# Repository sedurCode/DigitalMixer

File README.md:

View this project on [CADLAB.io](https://cadlab.io/project/1440). 

DigitalMixer

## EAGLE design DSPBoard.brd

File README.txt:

## WEBENCH Design 4
Created at Wed Nov 14 03:32:54 PST 2018
**********************************************************
***************** Schematic Instructions  ****************
**********************************************************

To import your new Schematic file into Eagle:

1. Unzip the downloaded folder files to local directory and Start Eagle.
2. Select "File"->"Open"->"Schematic..." from the menu at the top of
the screen.
3. Browse to your newly exported file and select the ".sch" file extension.
4. You should now see your schamtic available in Eagle.

**********************************************************
*******************  PCB Instructions  *******************
**********************************************************

To import your new BOARD file into Eagle:

1. Unzip the downloaded folder files to local directory and Start Eagle.
2. Select "File"->"Open"->"Board..." from the menu at the top of
the screen.
3. Browse to your newly exported file and select the ".brd" file extension.
4. Planes will need to be repoured to update the polygon fills
	1. Once your board is loaded, type "ratsnest" into the command
	   line and press the Enter key.
	2. The polygons should all be filled now.
5. You should now have an image of your board available in Eagle.

**********************************************************
*******************  LIB Instructions  *******************
**********************************************************

To import your new library into Eagle:

1. Start Eagle.
2. Select "File"->"New"->"Library" from the menu.
3. In the blank library window, select "File" -> "Execute Script"
from the menu.
5. Browse to your newly exported Eagle Script file (".scr" file extension)
6. After opening the file, the script will populate the new library.
Layer 93 should NOT exist.
7. Use "File"->Save As: "AcceleratedDesigns_Lib.lbr" and to the desired
location in Eagle native format.
8. Update schematic with the imported library, Select Library and click on Update; open the library file
	and sync. each part.

For additional information, please visit this site:
http://www.accelerated-designs.com/help/Eagle_import.html

You may also find this video helpful:
http://youtu.be/5jGuWY-Yy3Q

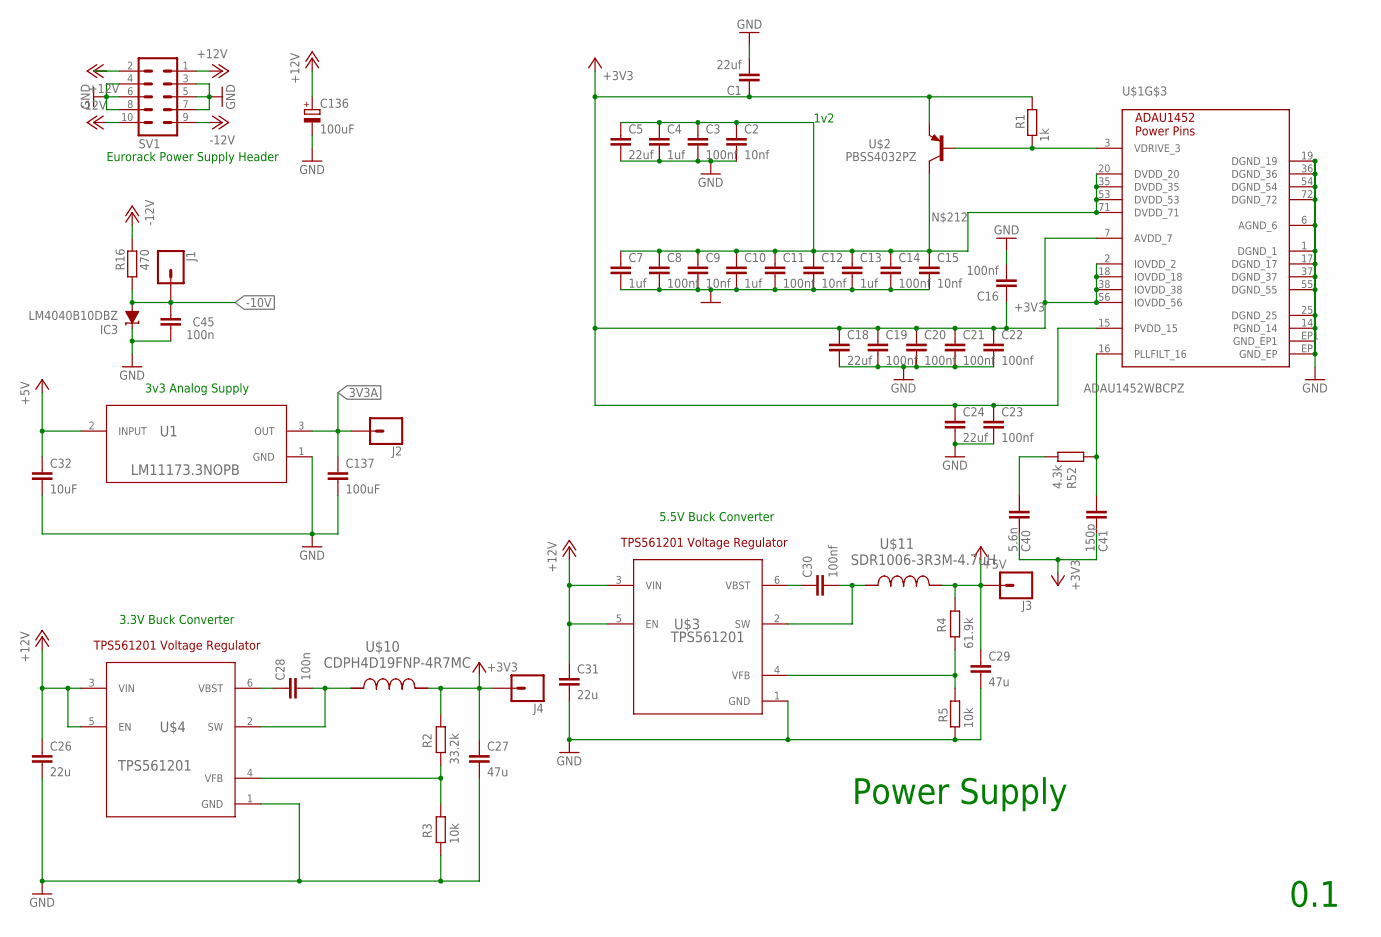
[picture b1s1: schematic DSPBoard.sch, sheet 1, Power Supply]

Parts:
C1, C5, C18, C24: 22uf; C0603
C2, C9, C12, C15: 10nf; C0603
C3, C8, C11, C14, C16, C19, C20, C21, C22, C23, C30: 100nf; C0603
C4, C7, C10, C13: 1uf; C0603
C26, C31: 22u; C0603
C27, C29: 47u; C0603
C28, C45: 100n; C0603
C32: 10uF; C0603
C40: 5.6n; C0603
C41: 150p; C0603
C136: 100uF; PANASONIC_D
C137: 100uF; C0603
IC3: LM4040B10DBZ; DBZ_R-PDSO-G3
J1, J2, J3, J4: CONN_01; 1X01
R1: 1k; R0603
R2: 33.2k; R0603
R3, R5: 10k; R0603
R4: 61.9k; R0603
R16: 470; R0603
R52: 4.3k; R0603
SV1: MA05-2
U1: LM11173.3NOPB; NDP0003B
U$1: ADAU1452WBCPZ; 72-LEADLFCSP_VQ
U$2: PBSS4032PZ; PG-SOT-223
U$3, U$4: TPS561201; DDC0006A
U$10: CDPH4D19FNP-4R7MC; CDPH4D19F
U$11: SDR1006-3R3M-4.7uH; SDR1006

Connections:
3V3A: C137.1, J2.1, U1.3 (OUT); also elsewhere on the board
+3V3: C1.1, C16.1, C18.1, C19.1, C20.1, C21.1, C22.1, C23.1, C24.1, C27.1, C40.2, C41.2, J4.1, R1.2, R2.1, U$1.2 (IOVDD_2), U$1.7 (AVDD_7), U$1.15 (PVDD_15), U$1.18 (IOVDD_18), U$1.38 (IOVDD_38), U$1.56 (IOVDD_56), U$2.3 (EMITTER_3), U$10.2; also elsewhere on the board
+5V: C29.1, C32.1, J3.1, R4.1, U1.2 (INPUT), U$11.2; also elsewhere on the board
+12V: C26.1, C31.1, C136.+, SV1.1, SV1.2, U$3.3 (VIN), U$3.5 (EN), U$4.3 (VIN), U$4.5 (EN); also elsewhere on the board
-10V: C45.2, IC3.2 (A), J1.1, R16.1; also elsewhere on the board
-12V: R16.2, SV1.9, SV1.10; also elsewhere on the board
GND: C1.2, C2.2, C3.2, C4.2, C5.2, C7.2, C8.2, C9.2, C10.2, C11.2, C12.2, C13.2, C14.2, C15.2, C16.2, C18.2, C19.2, C20.2, C21.2, C22.2, C23.2, C24.2, C26.2, C27.2, C29.2, C31.2, C32.2, C45.1, C136.-, C137.2, IC3.1 (C), R3.2, R5.2, SV1.3, SV1.4, SV1.5, SV1.6, SV1.7, SV1.8, U1.1 (GND), U$1.1 (DGND_1), U$1.6 (AGND_6), U$1.14 (PGND_14), U$1.17 (DGND_17), U$1.19 (DGND_19), U$1.25 (DGND_25), U$1.36 (DGND_36), U$1.37 (DGND_37), U$1.54 (DGND_54), U$1.55 (DGND_55), U$1.72 (DGND_72), U$1.EP (GND_EP), U$1.EP1 (GND_EP1), U$3.1 (GND), U$4.1 (GND); also elsewhere on the board
unnamed: R1.1, U$1.3 (VDRIVE_3), U$2.1 (BASE_1)
unnamed: C30.1, U$3.6 (VBST)
unnamed: C28.1, U$4.6 (VBST)
unnamed: C28.2, U$4.2 (SW), U$10.1
unnamed: C30.2, U$3.2 (SW), U$11.1
unnamed: R2.2, R3.1, U$4.4 (VFB)
unnamed: R4.2, R5.1, U$3.4 (VFB)
unnamed: C41.1, R52.2, U$1.16 (PLLFILT_16)
unnamed: C40.1, R52.1
unnamed: C2.1, C3.1, C4.1, C5.1, C7.1, C8.1, C9.1, C10.1, C11.1, C12.1, C13.1, C14.1, C15.1, U$1.20 (DVDD_20), U$1.35 (DVDD_35), U$1.53 (DVDD_53), U$1.71 (DVDD_71), U$2.2 (COLLECTOR_2,4), U$2.4 (COLLECTOR_2,4)

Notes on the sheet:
Power Supply
Eurorack Power Supply Header
5.5V Buck Converter
3.3V Buck Converter
3v3 Analog Supply
0.1
1v2

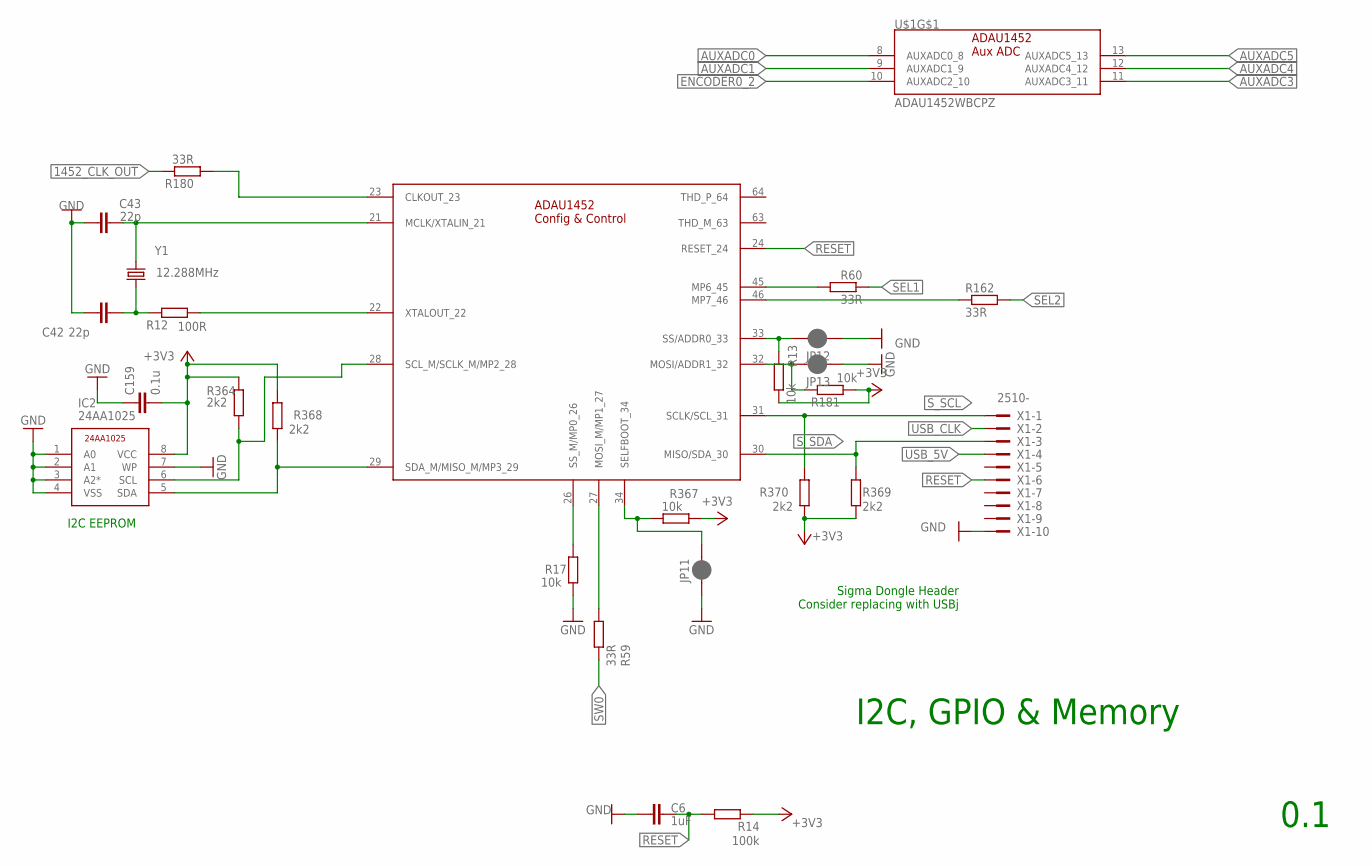
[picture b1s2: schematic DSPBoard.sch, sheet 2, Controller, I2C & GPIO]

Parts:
C6: 1uF; C0603
C42, C43: 22p; C0603
C159: 0.1u; C0603
IC2: 24AA1025; SOIC8
JP11, JP12, JP13: JUMPER-SMT_2_NC_PASTE_SILK; SMT-JUMPER_2_NC_PASTE_SILK
R12: 100R; R0603
R13, R17, R181, R367: 10k; R0603
R14: 100k; R0603
R59, R60, R162, R180: 33R; R0603
R364, R368, R369, R370: 2k2; R0603
U$1: ADAU1452WBCPZ; 72-LEADLFCSP_VQ
X1: 2510-; PAK100/2500-10
Y1: 12.288MHz; CRYSTAL-SMD-5X3.2-4PAD

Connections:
1452_CLK_OUT: R180.2; also elsewhere on the board
+3V3: C159.2, IC2.8 (VCC), R13.1, R14.2, R181.1, R364.2, R367.2, R368.1, R369.1, R370.1; also elsewhere on the board
AUXADC0: U$1.8 (AUXADC0_8); also elsewhere on the board
AUXADC1: U$1.9 (AUXADC1_9)
AUXADC3: U$1.11 (AUXADC3_11)
AUXADC4: U$1.12 (AUXADC4_12)
AUXADC5: U$1.13 (AUXADC5_13)
ENCODER0_2: U$1.10 (AUXADC2_10)
GND: C6.2, C42.1, C43.1, C159.1, IC2.1 (A0), IC2.2 (A1), IC2.3 (A2*), IC2.4 (VSS), IC2.7 (WP), JP11.1, JP12.1, JP13.1, R17.2, X1.10; also elsewhere on the board
MP0: R17.1, U$1.26 (SS_M/MP0_26)
MP1: R59.1, U$1.27 (MOSI_M/MP1_27)
MP2: IC2.6 (SCL), R364.1, U$1.28 (SCL_M/SCLK_M/MP2_28)
MP3: IC2.5 (SDA), R368.2, U$1.29 (SDA_M/MISO_M/MP3_29)
MP6: R60.2, U$1.45 (MP6_45)
MP7: R162.1, U$1.46 (MP7_46)
unnamed: R12.2, U$1.22 (XTALOUT_22)
unnamed: C43.2, U$1.21 (MCLK/XTALIN_21), Y1.3 (2)
unnamed: C42.2, R12.1, Y1.1
unnamed: R180.1, U$1.23 (CLKOUT_23)
unnamed: JP12.2, R13.2, U$1.33 (SS/ADDR0_33)
unnamed: JP13.2, R181.2, U$1.32 (MOSI/ADDR1_32)
unnamed: JP11.2, R367.1, U$1.34 (SELFBOOT_34)
RESET: C6.1, R14.1, U$1.24 (RESET_24), X1.6; also elsewhere on the board
SEL1: R60.1; also elsewhere on the board
SEL2: R162.2; also elsewhere on the board
SW0: R59.2; also elsewhere on the board
S_SCL: R370.2, U$1.31 (SCLK/SCL_31), X1.1; also elsewhere on the board
S_SDA: R369.2, U$1.30 (MISO/SDA_30), X1.3; also elsewhere on the board
USB_5V: X1.4
USB_CLK: X1.2

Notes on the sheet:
I2C EEPROM
Sigma Dongle Header Consider replacing with USBj
0.1
I2C, GPIO & Memory

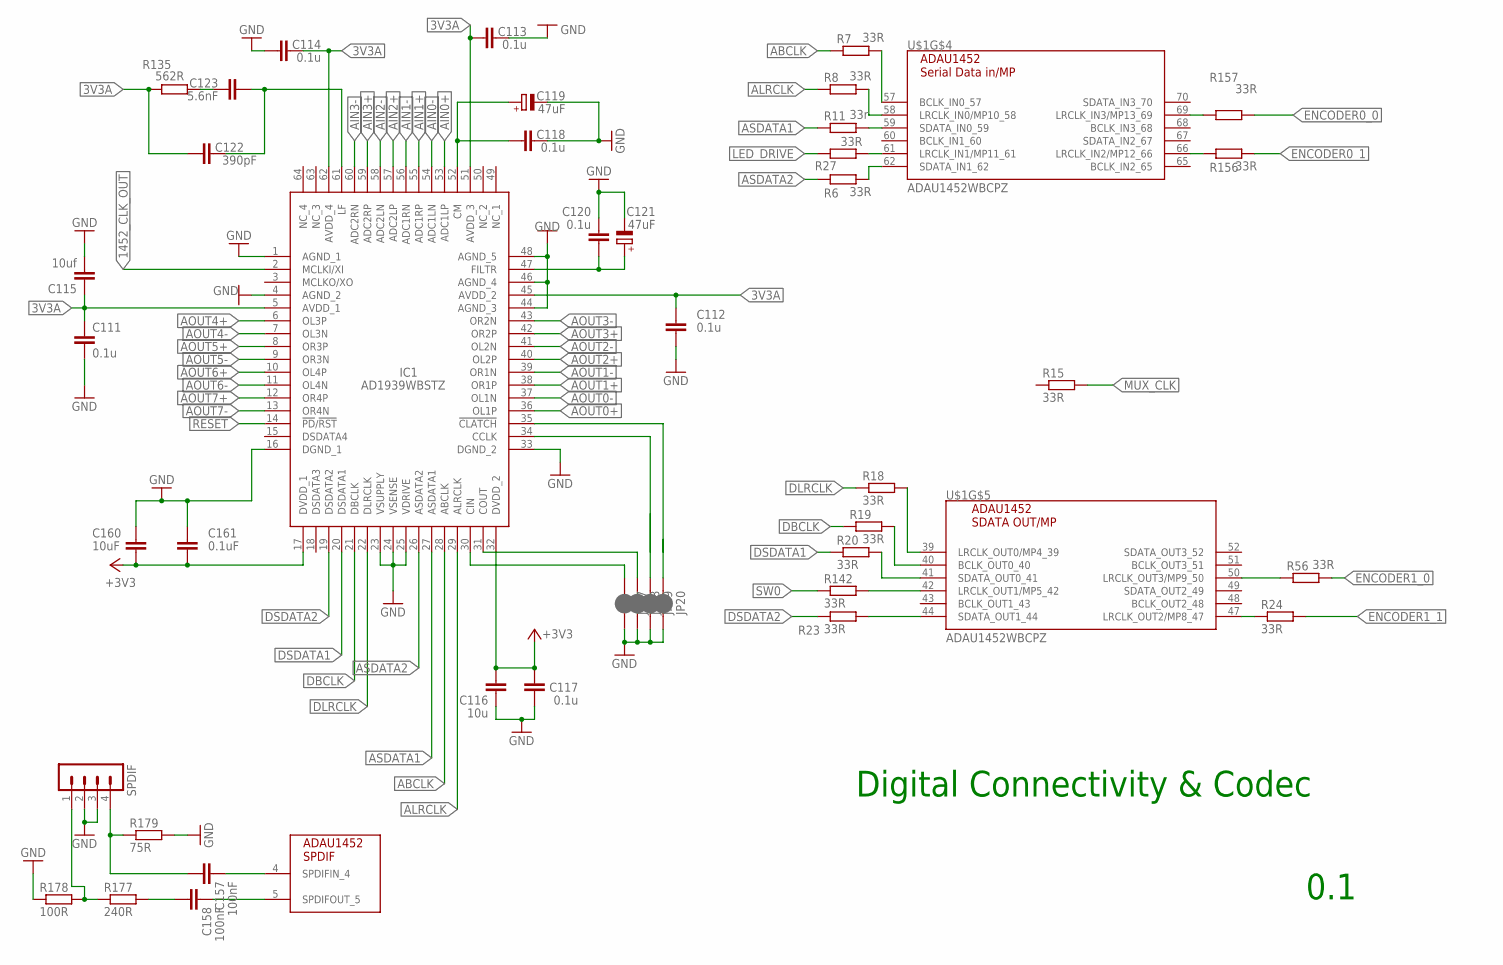
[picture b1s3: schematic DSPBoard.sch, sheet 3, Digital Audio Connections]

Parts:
C111, C112, C113, C114, C117, C118, C120: 0.1u; C0603
C115: 10uf; C0603
C116: 10u; C0603
C119, C121: 47uF; PANASONIC_D
C122: 390pF; C0603
C123: 5.6nF; C0603
C157, C158: 100nF; C0603
C160: 10uF; C0603
C161: 0.1uF; C0603
IC1: AD1939WBSTZ; QFP50P1200X1200X160-64N
JP17, JP18, JP19, JP20: JUMPER-SMT_2_NC_PASTE_SILK; SMT-JUMPER_2_NC_PASTE_SILK
R6, R7, R8, R15, R18, R19, R20, R23, R24, R27, R56, R142, R156, R157: 33R; R0603
R11: 33r; R0603
R135: 562R; R0603
R177: 240R; R0603
R178: 100R; R0603
R179: 75R; R0603
SPDIF: MA04-1
U$1: ADAU1452WBCPZ; 72-LEADLFCSP_VQ

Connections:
3V3A: C111.1, C112.1, C113.1, C114.2, C115.1, C122.1, IC1.5 (AVDD_1), IC1.45 (AVDD_2), IC1.51 (AVDD_3), IC1.62 (AVDD_4), R135.1; also elsewhere on the board
1452_CLK_OUT: IC1.2 (MCLKI/XI); also elsewhere on the board
+3V3: C116.2, C117.2, C160.2, C161.2, IC1.17 (DVDD_1), IC1.32 (DVDD_2); also elsewhere on the board
ABCLK: IC1.28 (ABCLK), R7.1
AIN0+: IC1.53 (ADC1LP); also elsewhere on the board
AIN0-: IC1.54 (ADC1LN); also elsewhere on the board
AIN1+: IC1.55 (ADC1RP); also elsewhere on the board
AIN1-: IC1.56 (ADC1RN); also elsewhere on the board
AIN2+: IC1.57 (ADC2LP); also elsewhere on the board
AIN2-: IC1.58 (ADC2LN); also elsewhere on the board
AIN3+: IC1.59 (ADC2RP); also elsewhere on the board
AIN3-: IC1.60 (ADC2RN); also elsewhere on the board
ALRCLK: IC1.29 (ALRCLK), R8.1
AOUT0+: IC1.36 (OL1P); also elsewhere on the board
AOUT0-: IC1.37 (OL1N); also elsewhere on the board
AOUT1+: IC1.38 (OR1P); also elsewhere on the board
AOUT1-: IC1.39 (OR1N); also elsewhere on the board
AOUT2+: IC1.40 (OL2P); also elsewhere on the board
AOUT2-: IC1.41 (OL2N); also elsewhere on the board
AOUT3+: IC1.42 (OR2P); also elsewhere on the board
AOUT3-: IC1.43 (OR2N); also elsewhere on the board
AOUT4+: IC1.6 (OL3P); also elsewhere on the board
AOUT4-: IC1.7 (OL3N); also elsewhere on the board
AOUT5+: IC1.8 (OR3P); also elsewhere on the board
AOUT5-: IC1.9 (OR3N); also elsewhere on the board
AOUT6+: IC1.10 (OL4P); also elsewhere on the board
AOUT6-: IC1.11 (OL4N); also elsewhere on the board
AOUT7+: IC1.12 (OR4P); also elsewhere on the board
AOUT7-: IC1.13 (OR4N); also elsewhere on the board
ASDATA1: IC1.27 (ASDATA1), R11.1
ASDATA2: IC1.26 (ASDATA2), R6.1
DBCLK: IC1.21 (DBCLK), R19.1
DLRCLK: IC1.22 (DLRCLK), R18.1
DSDATA1: IC1.20 (DSDATA1), R20.1
DSDATA2: IC1.19 (DSDATA2), R23.1
DSP_47: R24.1, U$1.47 (LRCLK_OUT2/MP8_47)
DSP_50: R56.1, U$1.50 (LRCLK_OUT3/MP9_50)
ENCODER0_0: R157.2; also elsewhere on the board
ENCODER0_1: R156.2; also elsewhere on the board
ENCODER1_0: R56.2; also elsewhere on the board
ENCODER1_1: R24.2; also elsewhere on the board
FILTR: C120.1, C121.+, IC1.47 (FILTR)
GND: C111.2, C112.2, C113.2, C114.1, C115.2, C116.1, C117.1, C118.2, C119.-, C120.2, C121.-, C160.1, C161.1, IC1.1 (AGND_1), IC1.4 (AGND_2), IC1.16 (DGND_1), IC1.23 (VSUPPLY), IC1.24 (VSENSE), IC1.25 (VDRIVE), IC1.33 (DGND_2), IC1.44 (AGND_3), IC1.46 (AGND_4), IC1.48 (AGND_5), JP17.2, JP18.2, JP19.2, JP20.2, R178.1, R179.2, SPDIF.2, SPDIF.3; also elsewhere on the board
LED_DRIVE: R27.2; also elsewhere on the board
MP4: R18.2, U$1.39 (LRCLK_OUT0/MP4_39)
MP5: R142.2, U$1.42 (LRCLK_OUT1/MP5_42)
MP10: R8.2, U$1.58 (LRCLK_IN0/MP10_58)
MP11: R27.1, U$1.61 (LRCLK_IN1/MP11_61)
MUX_CLK: R15.2; also elsewhere on the board
unnamed: IC1.30 (CIN), JP17.1
unnamed: R156.1, U$1.66 (LRCLK_IN2/MP12_66)
unnamed: R157.1, U$1.69 (LRCLK_IN3/MP13_69)
unnamed: C157.1, U$1.4 (SPDIFIN_4)
unnamed: C158.1, U$1.5 (SPDIFOUT_5)
unnamed: R6.2, U$1.62 (SDATA_IN1_62)
unnamed: C157.2, R179.1, SPDIF.4
unnamed: C118.1, C119.+, IC1.52 (CM)
unnamed: R7.2, U$1.57 (BCLK_IN0_57)
unnamed: C123.1, R135.2
unnamed: C122.2, C123.2, IC1.61 (LF)
unnamed: R11.2, U$1.59 (SDATA_IN0_59)
unnamed: R23.2, U$1.44 (SDATA_OUT1_44)
unnamed: R20.2, U$1.41 (SDATA_OUT0_41)
unnamed: R19.2, U$1.40 (BCLK_OUT0_40)
unnamed: C158.2, R177.2
unnamed: R177.1, R178.2, SPDIF.1
unnamed: IC1.31 (COUT), JP18.1
RESET: IC1.14 (!PD!/!RST); also elsewhere on the board
SW0: R142.1; also elsewhere on the board

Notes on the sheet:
0.1
Digital Connectivity & Codec

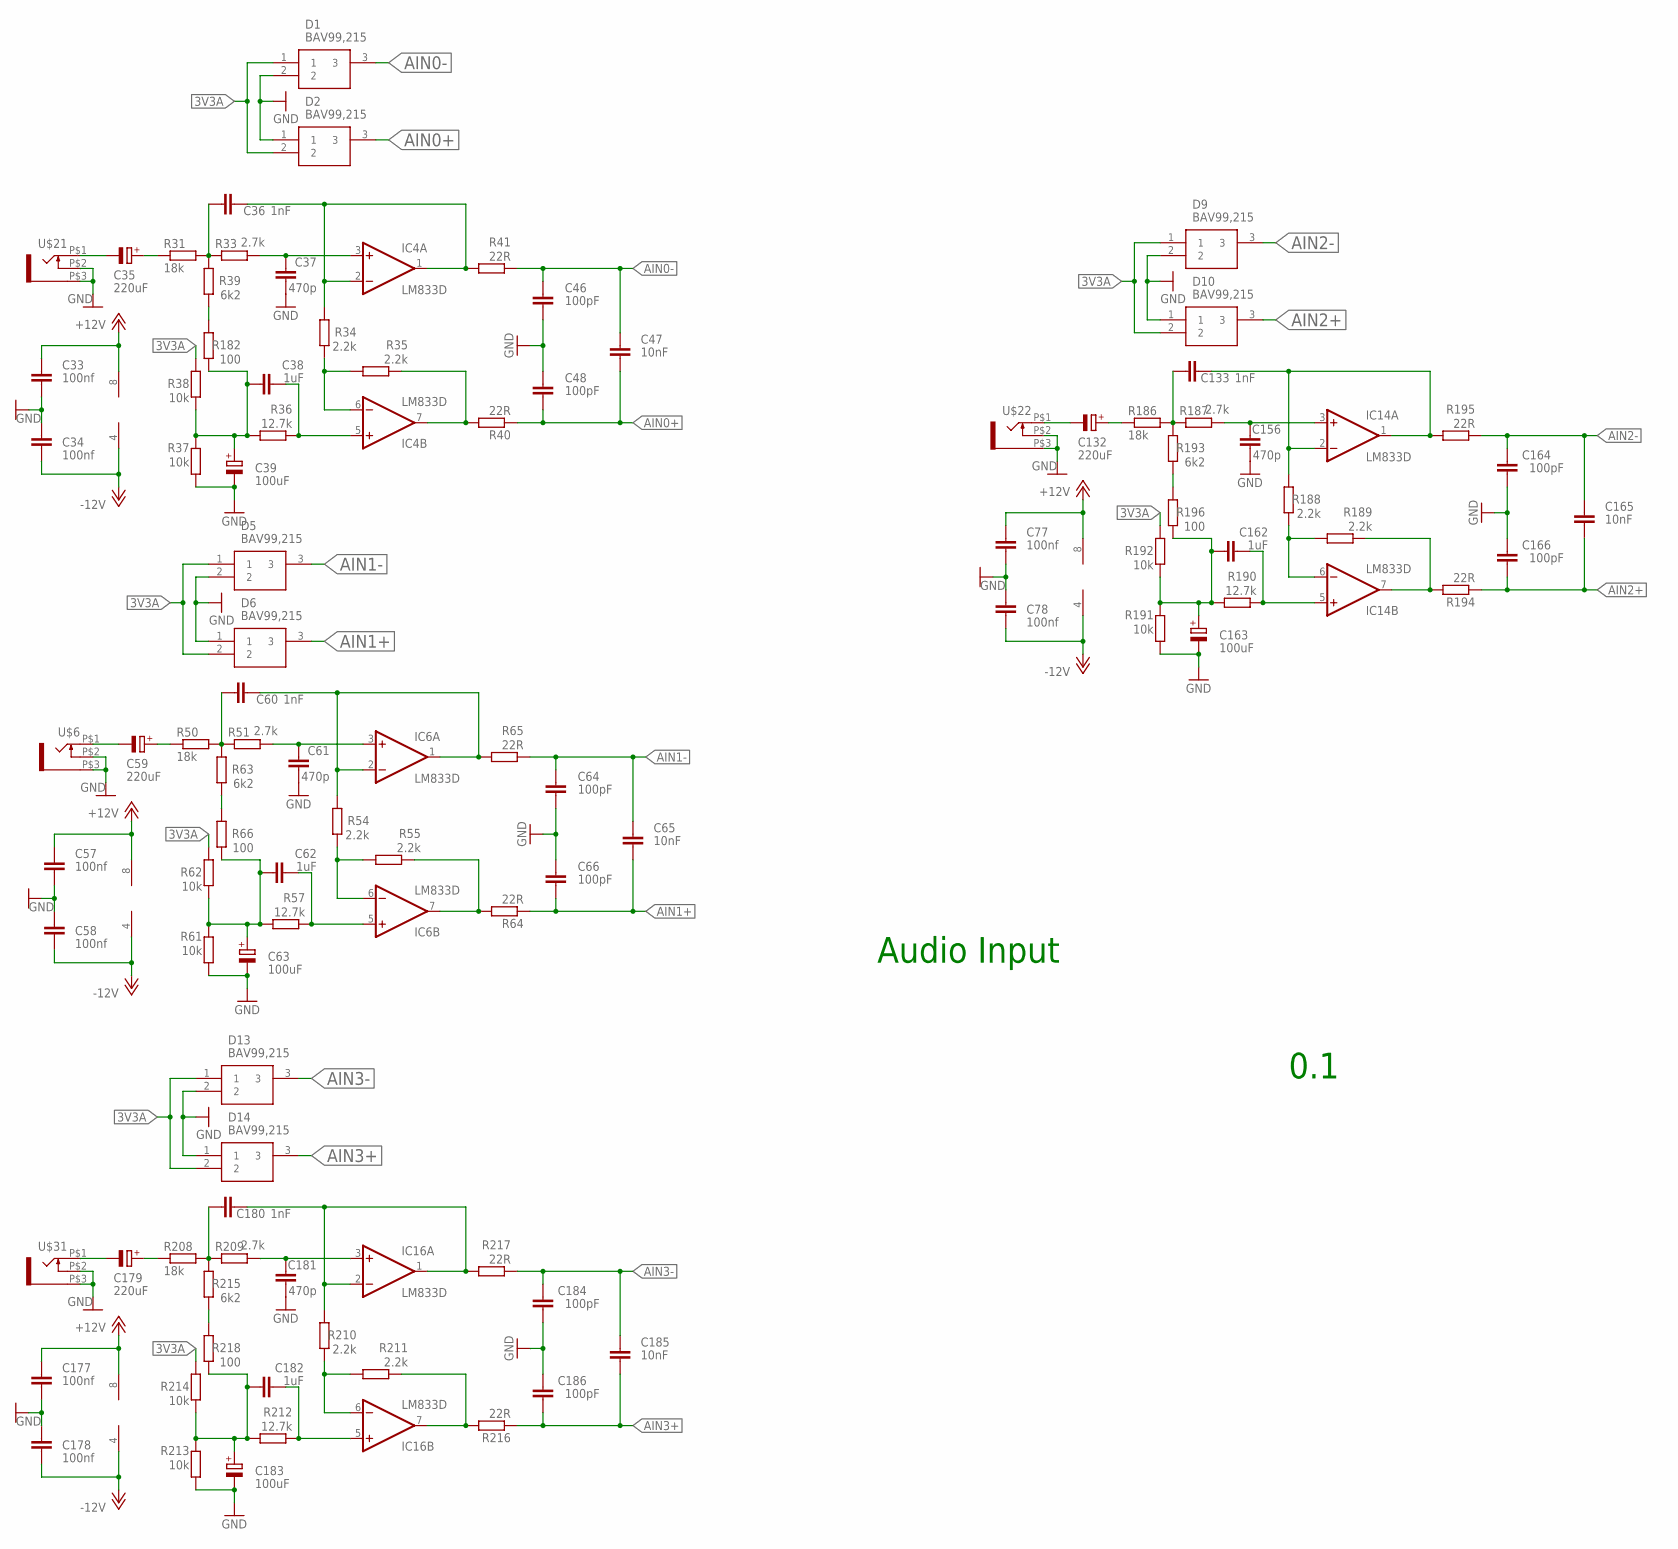
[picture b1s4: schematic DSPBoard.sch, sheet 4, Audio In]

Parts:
C33, C34, C57, C58, C77, C78, C177, C178: 100nf; C0603
C35, C59, C132, C179: 220uF; PANASONIC_D
C36, C60, C133, C180: 1nF; C0603
C37, C61, C156, C181: 470p; C0603
C38, C62, C162, C182: 1uF; C0603
C39, C63, C163, C183: 100uF; PANASONIC_D
C46, C48, C64, C66, C164, C166, C184, C186: 100pF; C0603
C47, C65, C165, C185: 10nF; C0603
D1, D2, D5, D6, D9, D10, D13, D14: BAV99,215; SOT95P230X110-3N
IC4, IC6, IC14, IC16: LM833D; SO08
R31, R50, R186, R208: 18k; R0603
R33, R51, R187, R209: 2.7k; R0603
R34, R35, R54, R55, R188, R189, R210, R211: 2.2k; R0603
R36, R57, R190, R212: 12.7k; R0603
R37, R38, R61, R62, R191, R192, R213, R214: 10k; R0603
R39, R63, R193, R215: 6k2; R0603
R40, R41, R64, R65, R194, R195, R216, R217: 22R; R0603
R66, R182, R196, R218: 100; R0603
U$6, U$21, U$22, U$31: WQP-PJ301M-12_JACK

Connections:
3V3A: D1.1, D2.2, D5.1, D6.2, D9.1, D10.2, D13.1, D14.2, R38.2, R62.2, R192.2, R214.2; also elsewhere on the board
+12V: C33.1, C57.1, C77.1, C177.1, IC4.8 (V+), IC6.8 (V+), IC14.8 (V+), IC16.8 (V+); also elsewhere on the board
-12V: C34.2, C58.2, C78.2, C178.2, IC4.4 (V-), IC6.4 (V-), IC14.4 (V-), IC16.4 (V-); also elsewhere on the board
AIN0+: C47.2, C48.1, D2.3, R40.1; also elsewhere on the board
AIN0-: C46.2, C47.1, D1.3, R41.1; also elsewhere on the board
AIN1+: C65.2, C66.1, D6.3, R64.1; also elsewhere on the board
AIN1-: C64.2, C65.1, D5.3, R65.1; also elsewhere on the board
AIN2+: C165.2, C166.1, D10.3, R194.1; also elsewhere on the board
AIN2-: C164.2, C165.1, D9.3, R195.1; also elsewhere on the board
AIN3+: C185.2, C186.1, D14.3, R216.1; also elsewhere on the board
AIN3-: C184.2, C185.1, D13.3, R217.1; also elsewhere on the board
GND: C33.2, C34.1, C37.1, C39.-, C46.1, C48.2, C57.2, C58.1, C61.1, C63.-, C64.1, C66.2, C77.2, C78.1, C156.1, C163.-, C164.1, C166.2, C177.2, C178.1, C181.1, C183.-, C184.1, C186.2, D1.2, D2.1, D5.2, D6.1, D9.2, D10.1, D13.2, D14.1, R37.1, R61.1, R191.1, R213.1, U$6.P$2 (3), U$6.P$3 (1), U$21.P$2 (3), U$21.P$3 (1), U$22.P$2 (3), U$22.P$3 (1), U$31.P$2 (3), U$31.P$3 (1); also elsewhere on the board
unnamed: C35.-, U$21.P$1 (2)
unnamed: C35.+, R31.1
unnamed: C36.1, R31.2, R33.1, R39.2
unnamed: C37.2, IC4.3 (+IN), R33.2
unnamed: IC4.6 (-IN), R34.1, R35.2
unnamed: C36.2, IC4.1 (OUT), IC4.2 (-IN), R34.2, R41.2
unnamed: IC4.7 (OUT), R35.1, R40.2
unnamed: C38.2, IC4.5 (+IN), R36.1
unnamed: C38.1, C39.+, R36.2, R37.2, R38.1, R182.1
unnamed: C60.1, R50.2, R51.1, R63.2
unnamed: C61.2, IC6.3 (+IN), R51.2
unnamed: C60.2, IC6.1 (OUT), IC6.2 (-IN), R54.2, R65.2
unnamed: IC6.6 (-IN), R54.1, R55.2
unnamed: IC6.7 (OUT), R55.1, R64.2
unnamed: C62.2, IC6.5 (+IN), R57.1
unnamed: C62.1, C63.+, R57.2, R61.2, R62.1, R66.1
unnamed: C59.-, U$6.P$1 (2)
unnamed: C59.+, R50.1
unnamed: R63.1, R66.2
unnamed: R39.1, R182.2
unnamed: C133.1, R186.2, R187.1, R193.2
unnamed: C156.2, IC14.3 (+IN), R187.2
unnamed: C133.2, IC14.1 (OUT), IC14.2 (-IN), R188.2, R195.2
unnamed: IC14.6 (-IN), R188.1, R189.2
unnamed: IC14.7 (OUT), R189.1, R194.2
unnamed: C162.2, IC14.5 (+IN), R190.1
unnamed: C162.1, C163.+, R190.2, R191.2, R192.1, R196.1
unnamed: C132.-, U$22.P$1 (2)
unnamed: C132.+, R186.1
unnamed: R193.1, R196.2
unnamed: C180.1, R208.2, R209.1, R215.2
unnamed: C181.2, IC16.3 (+IN), R209.2
unnamed: C180.2, IC16.1 (OUT), IC16.2 (-IN), R210.2, R217.2
unnamed: IC16.6 (-IN), R210.1, R211.2
unnamed: IC16.7 (OUT), R211.1, R216.2
unnamed: C182.2, IC16.5 (+IN), R212.1
unnamed: C182.1, C183.+, R212.2, R213.2, R214.1, R218.1
unnamed: C179.-, U$31.P$1 (2)
unnamed: C179.+, R208.1
unnamed: R215.1, R218.2

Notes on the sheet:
0.1
Audio Input

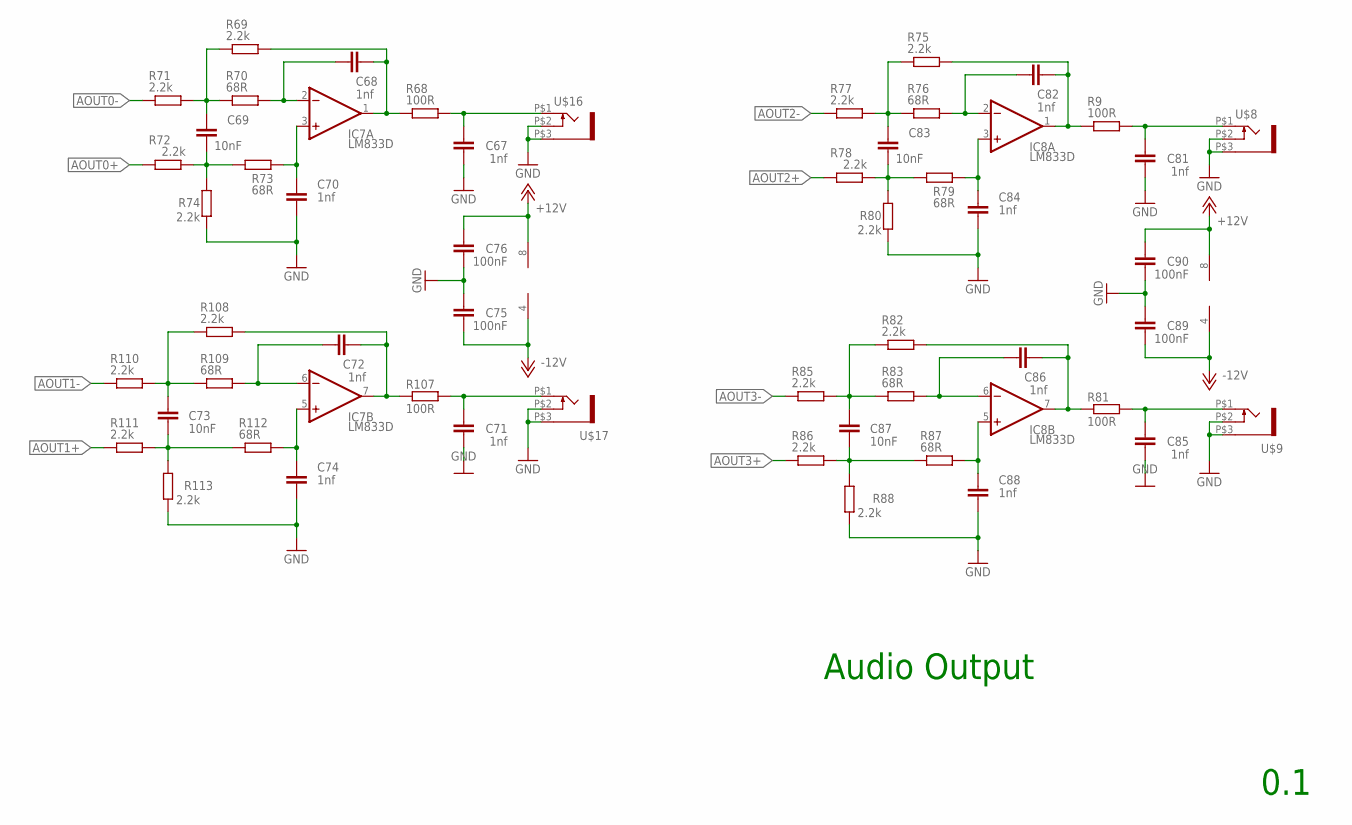
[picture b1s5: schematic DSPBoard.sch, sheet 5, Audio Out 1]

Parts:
C67, C68, C70, C71, C72, C74, C81, C82, C84, C85, C86, C88: 1nf; C0603
C69, C73, C83, C87: 10nF; C0603
C75, C76, C89, C90: 100nF; C0603
IC7, IC8: LM833D; SO08
R9, R68, R81, R107: 100R; R0603
R69, R71, R72, R74, R75, R77, R78, R80, R82, R85, R86, R88, R108, R110, R111, R113: 2.2k; R0603
R70, R73, R76, R79, R83, R87, R109, R112: 68R; R0603
U$8, U$9, U$16, U$17: WQP-PJ301M-12_JACK

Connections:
+12V: C76.2, C90.2, IC7.8 (V+), IC8.8 (V+); also elsewhere on the board
-12V: C75.1, C89.1, IC7.4 (V-), IC8.4 (V-); also elsewhere on the board
AOUT0+: R72.1; also elsewhere on the board
AOUT0-: R71.1; also elsewhere on the board
AOUT1+: R111.1; also elsewhere on the board
AOUT1-: R110.1; also elsewhere on the board
AOUT2+: R78.1; also elsewhere on the board
AOUT2-: R77.1; also elsewhere on the board
AOUT3+: R86.1; also elsewhere on the board
AOUT3-: R85.1; also elsewhere on the board
GND: C67.1, C70.2, C71.1, C74.2, C75.2, C76.1, C81.1, C84.2, C85.1, C88.2, C89.2, C90.1, R74.1, R80.1, R88.1, R113.1, U$8.P$2 (3), U$8.P$3 (1), U$9.P$2 (3), U$9.P$3 (1), U$16.P$2 (3), U$16.P$3 (1), U$17.P$2 (3), U$17.P$3 (1); also elsewhere on the board
unnamed: C72.2, IC7.6 (-IN), R109.2
unnamed: C73.1, R108.1, R109.1, R110.2
unnamed: C73.2, R111.2, R112.1, R113.2
unnamed: C72.1, IC7.7 (OUT), R107.1, R108.2
unnamed: C74.1, IC7.5 (+IN), R112.2
unnamed: C71.2, R107.2, U$17.P$1 (2)
unnamed: C67.2, R68.2, U$16.P$1 (2)
unnamed: C68.1, IC7.1 (OUT), R68.1, R69.2
unnamed: C68.2, IC7.2 (-IN), R70.2
unnamed: C69.1, R69.1, R70.1, R71.2
unnamed: C69.2, R72.2, R73.1, R74.2
unnamed: C70.1, IC7.3 (+IN), R73.2
unnamed: C86.2, IC8.6 (-IN), R83.2
unnamed: C87.1, R82.1, R83.1, R85.2
unnamed: C87.2, R86.2, R87.1, R88.2
unnamed: C86.1, IC8.7 (OUT), R81.1, R82.2
unnamed: C88.1, IC8.5 (+IN), R87.2
unnamed: C85.2, R81.2, U$9.P$1 (2)
unnamed: C81.2, R9.2, U$8.P$1 (2)
unnamed: C82.1, IC8.1 (OUT), R9.1, R75.2
unnamed: C82.2, IC8.2 (-IN), R76.2
unnamed: C83.1, R75.1, R76.1, R77.2
unnamed: C83.2, R78.2, R79.1, R80.2
unnamed: C84.1, IC8.3 (+IN), R79.2

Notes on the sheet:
0.1
Audio Output

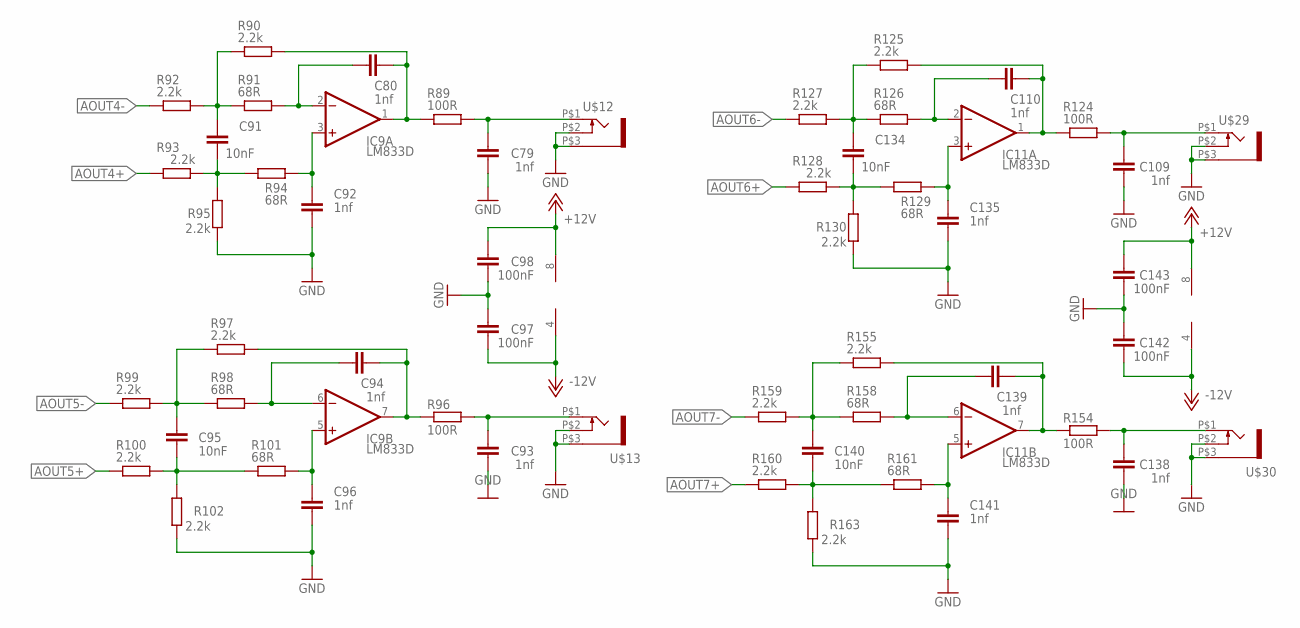
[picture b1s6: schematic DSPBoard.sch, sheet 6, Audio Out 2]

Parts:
C79, C80, C92, C93, C94, C96, C109, C110, C135, C138, C139, C141: 1nf; C0603
C91, C95, C134, C140: 10nF; C0603
C97, C98, C142, C143: 100nF; C0603
IC9, IC11: LM833D; SO08
R89, R96, R124, R154: 100R; R0603
R90, R92, R93, R95, R97, R99, R100, R102, R125, R127, R128, R130, R155, R159, R160, R163: 2.2k; R0603
R91, R94, R98, R101, R126, R129, R158, R161: 68R; R0603
U$12, U$13, U$29, U$30: WQP-PJ301M-12_JACK

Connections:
+12V: C98.2, C143.2, IC9.8 (V+), IC11.8 (V+); also elsewhere on the board
-12V: C97.1, C142.1, IC9.4 (V-), IC11.4 (V-); also elsewhere on the board
AOUT4+: R93.1; also elsewhere on the board
AOUT4-: R92.1; also elsewhere on the board
AOUT5+: R100.1; also elsewhere on the board
AOUT5-: R99.1; also elsewhere on the board
AOUT6+: R128.1; also elsewhere on the board
AOUT6-: R127.1; also elsewhere on the board
AOUT7+: R160.1; also elsewhere on the board
AOUT7-: R159.1; also elsewhere on the board
GND: C79.1, C92.2, C93.1, C96.2, C97.2, C98.1, C109.1, C135.2, C138.1, C141.2, C142.2, C143.1, R95.1, R102.1, R130.1, R163.1, U$12.P$2 (3), U$12.P$3 (1), U$13.P$2 (3), U$13.P$3 (1), U$29.P$2 (3), U$29.P$3 (1), U$30.P$2 (3), U$30.P$3 (1); also elsewhere on the board
unnamed: C94.2, IC9.6 (-IN), R98.2
unnamed: C95.1, R97.1, R98.1, R99.2
unnamed: C95.2, R100.2, R101.1, R102.2
unnamed: C94.1, IC9.7 (OUT), R96.1, R97.2
unnamed: C96.1, IC9.5 (+IN), R101.2
unnamed: C93.2, R96.2, U$13.P$1 (2)
unnamed: C79.2, R89.2, U$12.P$1 (2)
unnamed: C80.1, IC9.1 (OUT), R89.1, R90.2
unnamed: C80.2, IC9.2 (-IN), R91.2
unnamed: C91.1, R90.1, R91.1, R92.2
unnamed: C91.2, R93.2, R94.1, R95.2
unnamed: C92.1, IC9.3 (+IN), R94.2
unnamed: C139.2, IC11.6 (-IN), R158.2
unnamed: C140.1, R155.1, R158.1, R159.2
unnamed: C140.2, R160.2, R161.1, R163.2
unnamed: C139.1, IC11.7 (OUT), R154.1, R155.2
unnamed: C141.1, IC11.5 (+IN), R161.2
unnamed: C138.2, R154.2, U$30.P$1 (2)
unnamed: C109.2, R124.2, U$29.P$1 (2)
unnamed: C110.1, IC11.1 (OUT), R124.1, R125.2
unnamed: C110.2, IC11.2 (-IN), R126.2
unnamed: C134.1, R125.1, R126.1, R127.2
unnamed: C134.2, R128.2, R129.1, R130.2
unnamed: C135.1, IC11.3 (+IN), R129.2

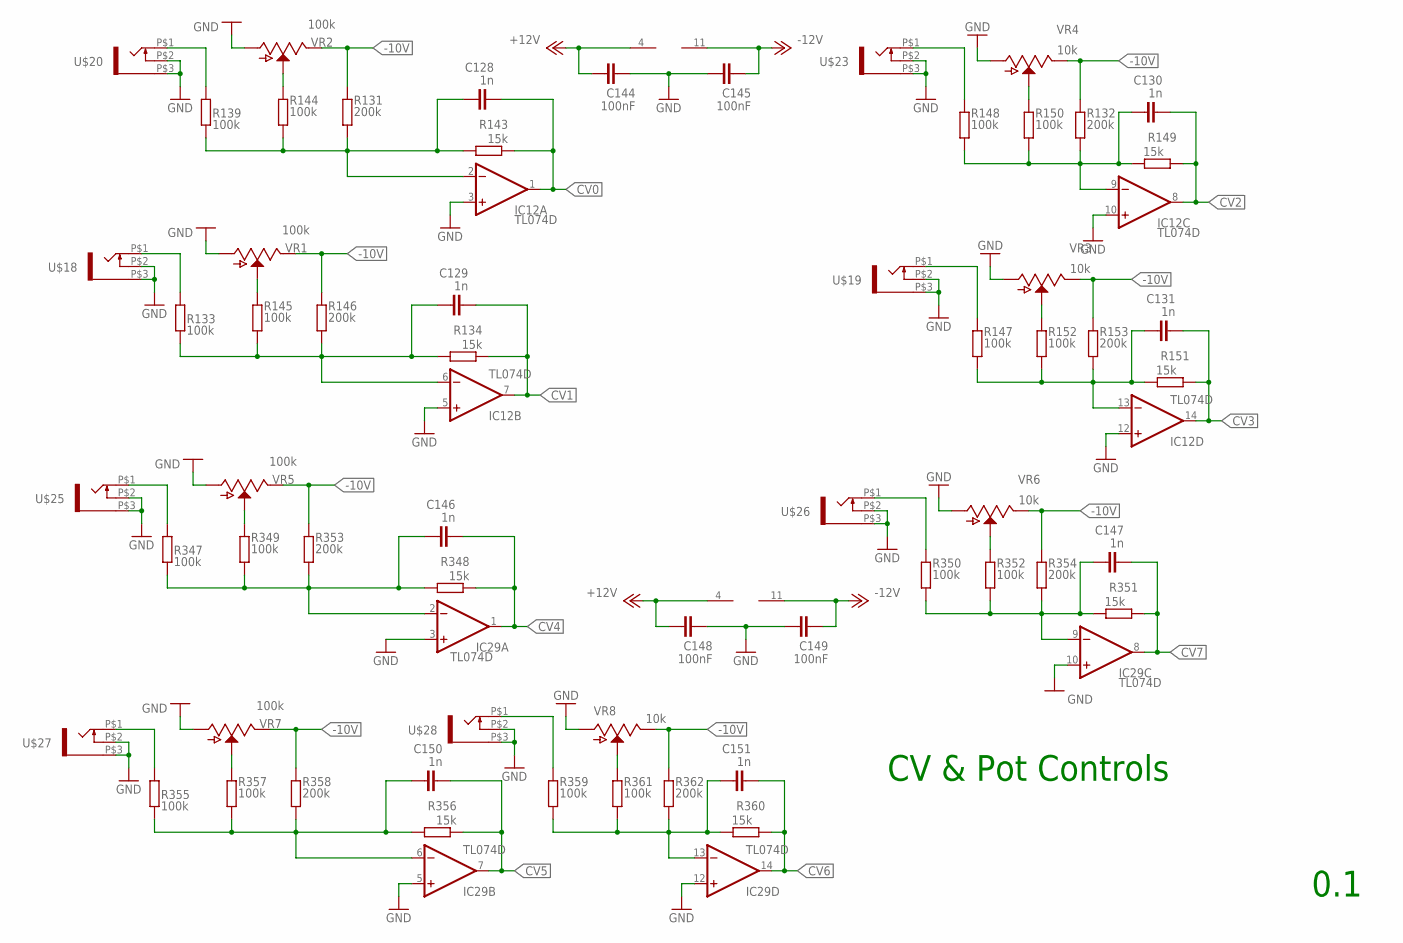
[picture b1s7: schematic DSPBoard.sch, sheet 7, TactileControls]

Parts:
C128, C129, C130, C131, C146, C147, C150, C151: 1n; C0603
C144, C145, C148, C149: 100nF; C0603
IC12, IC29: TL074D; SO14
R131, R132, R146, R153, R353, R354, R358, R362: 200k; R0603
R133, R139, R144, R145, R147, R148, R150, R152, R347, R349, R350, R352, R355, R357, R359, R361: 100k; R0603
R134, R143, R149, R151, R348, R351, R356, R360: 15k; R0603
U$18, U$19, U$20, U$23, U$25, U$26, U$27, U$28: WQP-PJ301M-12_JACK
VR1, VR2, VR5, VR7: 100k; POT-PTH-ALPS-KIT
VR3, VR4, VR6, VR8: 10k; POT-PTH-ALPS-KIT

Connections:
+12V: C144.1, C148.1, IC12.4 (V+), IC29.4 (V+); also elsewhere on the board
-10V: R131.1, R132.1, R146.1, R153.1, R353.1, R354.1, R358.1, R362.1, VR1.P$1 (E), VR2.P$1 (E), VR3.P$1 (E), VR4.P$1 (E), VR5.P$1 (E), VR6.P$1 (E), VR7.P$1 (E), VR8.P$1 (E); also elsewhere on the board
-12V: C145.2, C149.2, IC12.11 (V-), IC29.11 (V-); also elsewhere on the board
CV0: C128.2, IC12.1 (OUT), R143.1; also elsewhere on the board
CV1: C129.2, IC12.7 (OUT), R134.1; also elsewhere on the board
CV2: C130.2, IC12.8 (OUT), R149.1; also elsewhere on the board
CV3: C131.2, IC12.14 (OUT), R151.1; also elsewhere on the board
CV4: C146.2, IC29.1 (OUT), R348.1; also elsewhere on the board
CV5: C150.2, IC29.7 (OUT), R356.1; also elsewhere on the board
CV6: C151.2, IC29.14 (OUT), R360.1; also elsewhere on the board
CV7: C147.2, IC29.8 (OUT), R351.1; also elsewhere on the board
GND: C144.2, C145.1, C148.2, C149.1, IC12.3 (+IN), IC12.5 (+IN), IC12.10 (+IN), IC12.12 (+IN), IC29.3 (+IN), IC29.5 (+IN), IC29.10 (+IN), IC29.12 (+IN), U$18.P$2 (3), U$18.P$3 (1), U$19.P$2 (3), U$19.P$3 (1), U$20.P$2 (3), U$20.P$3 (1), U$23.P$2 (3), U$23.P$3 (1), U$25.P$2 (3), U$25.P$3 (1), U$26.P$2 (3), U$26.P$3 (1), U$27.P$2 (3), U$27.P$3 (1), U$28.P$2 (3), U$28.P$3 (1), VR1.P$3 (A), VR2.P$3 (A), VR3.P$3 (A), VR4.P$3 (A), VR5.P$3 (A), VR6.P$3 (A), VR7.P$3 (A), VR8.P$3 (A); also elsewhere on the board
unnamed: R144.1, VR2.P$2 (S)
unnamed: R139.1, U$20.P$1 (2)
unnamed: R148.1, U$23.P$1 (2)
unnamed: C128.1, IC12.2 (-IN), R131.2, R139.2, R143.2, R144.2
unnamed: R150.1, VR4.P$2 (S)
unnamed: C130.1, IC12.9 (-IN), R132.2, R148.2, R149.2, R150.2
unnamed: R145.1, VR1.P$2 (S)
unnamed: R133.1, U$18.P$1 (2)
unnamed: C129.1, IC12.6 (-IN), R133.2, R134.2, R145.2, R146.2
unnamed: R147.1, U$19.P$1 (2)
unnamed: R152.1, VR3.P$2 (S)
unnamed: C131.1, IC12.13 (-IN), R147.2, R151.2, R152.2, R153.2
unnamed: R349.1, VR5.P$2 (S)
unnamed: R347.1, U$25.P$1 (2)
unnamed: C146.1, IC29.2 (-IN), R347.2, R348.2, R349.2, R353.2
unnamed: R350.1, U$26.P$1 (2)
unnamed: R352.1, VR6.P$2 (S)
unnamed: C147.1, IC29.9 (-IN), R350.2, R351.2, R352.2, R354.2
unnamed: R357.1, VR7.P$2 (S)
unnamed: R355.1, U$27.P$1 (2)
unnamed: C150.1, IC29.6 (-IN), R355.2, R356.2, R357.2, R358.2
unnamed: R359.1, U$28.P$1 (2)
unnamed: R361.1, VR8.P$2 (S)
unnamed: C151.1, IC29.13 (-IN), R359.2, R360.2, R361.2, R362.2

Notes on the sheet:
0.1
CV & Pot Controls

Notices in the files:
parts and their libraries:
SparkFun-Connectors: Licensing: Creative Commons ShareAlike 4.0 International - https://creativecommons.org/licenses/by-sa/4.0
Particle-Devices: Licensing: Designed by Particle.
